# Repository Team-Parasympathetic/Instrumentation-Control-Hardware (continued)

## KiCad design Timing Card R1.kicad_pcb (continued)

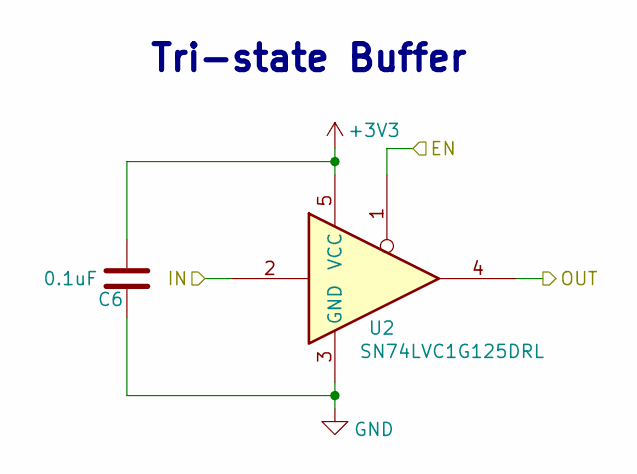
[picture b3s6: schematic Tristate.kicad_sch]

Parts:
C6: 0.1uF; C_0805_2012Metric
U2: SN74LVC1G125DRL; Texas_R-PDSO-N5_DRL-5

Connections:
/FPGA/CS: U2.1; also elsewhere on the board
/FPGA/SO/SPISO: U2.2; also elsewhere on the board
/FPGA/Tristate/OUT: U2.4; also elsewhere on the board

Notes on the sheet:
Tri-state Buffer

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
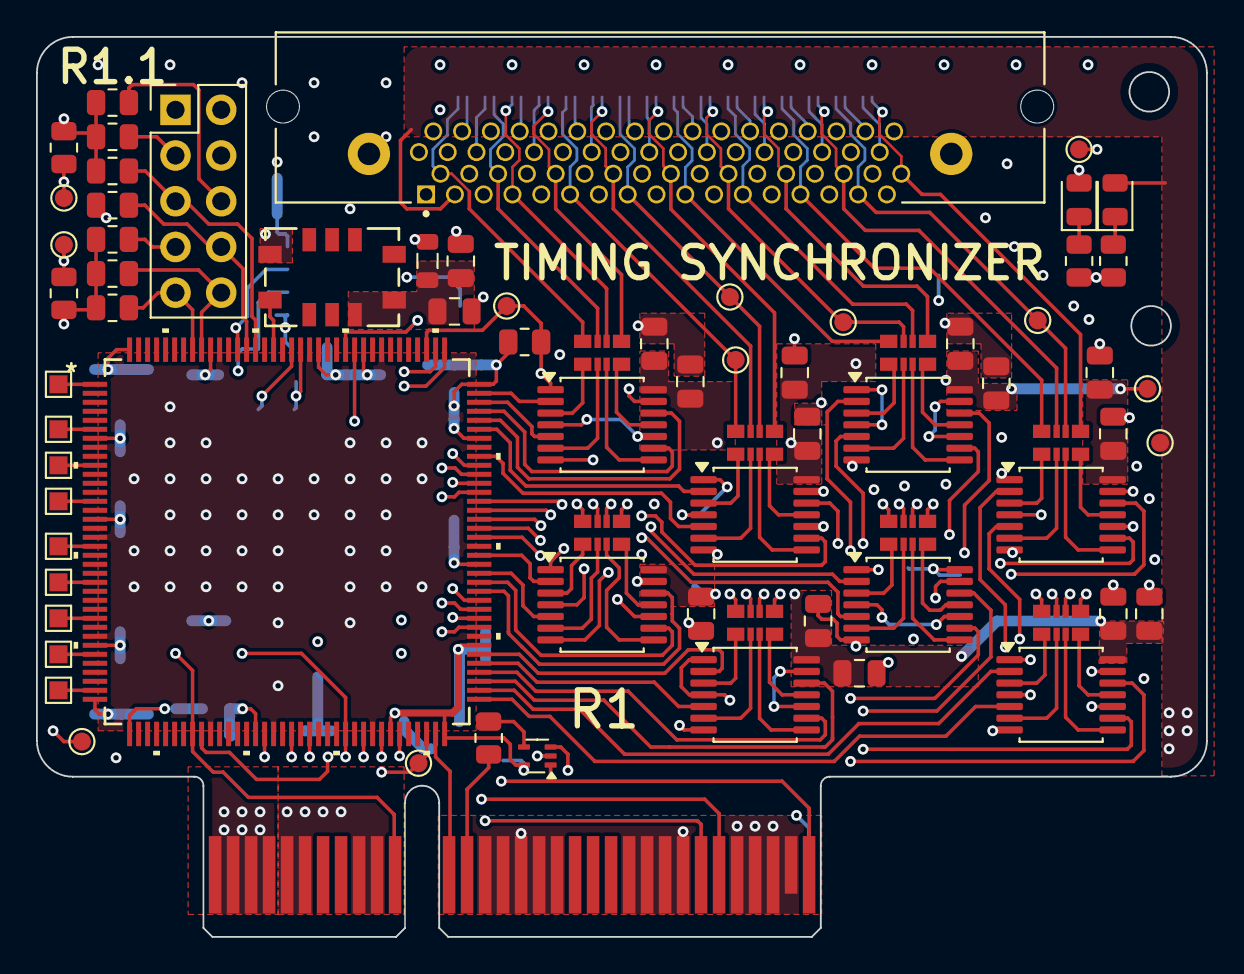
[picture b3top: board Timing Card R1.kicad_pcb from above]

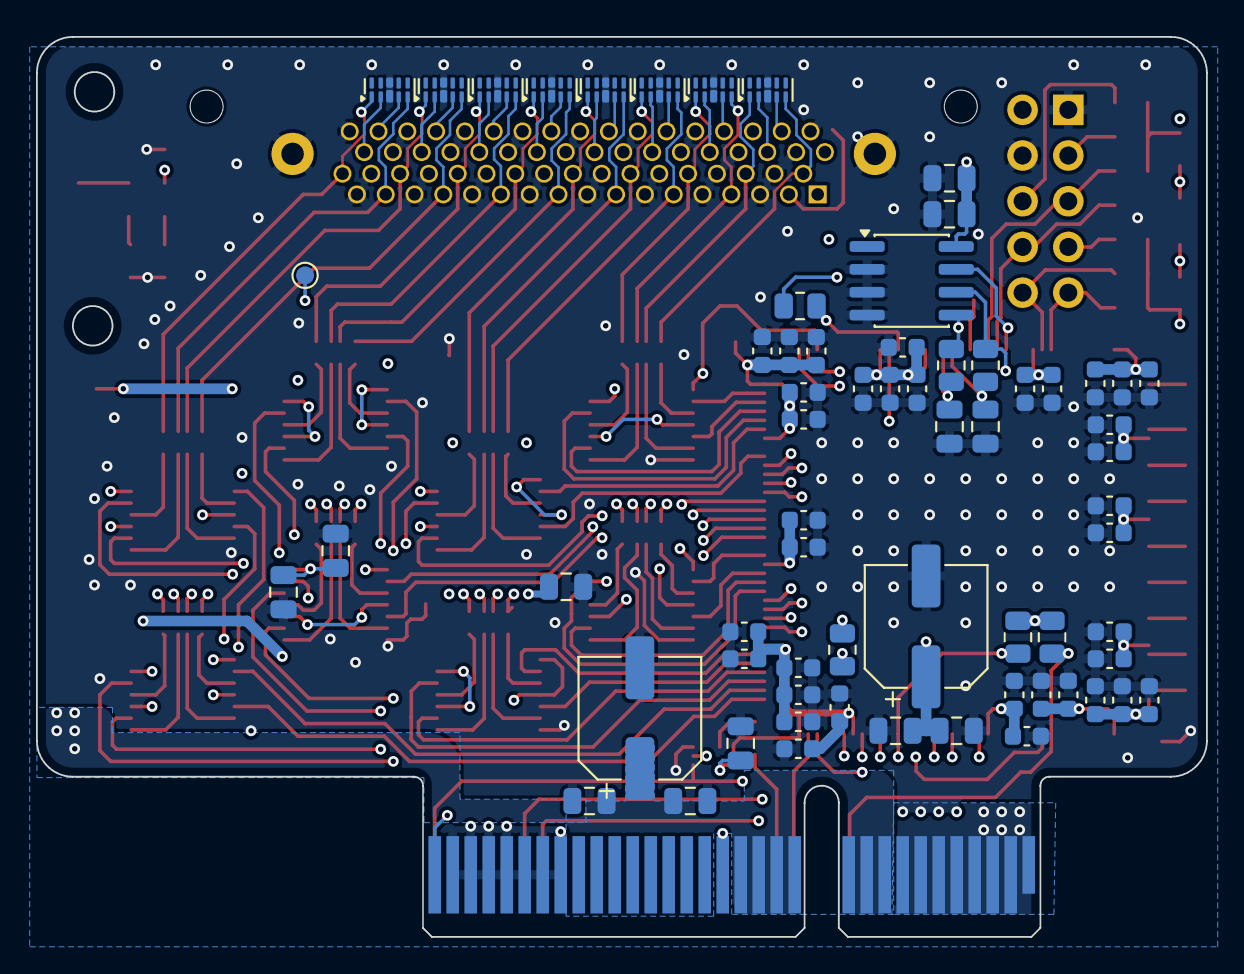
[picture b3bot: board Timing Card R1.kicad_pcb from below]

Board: 4 copper layers, 65.0 x 50.0 mm, 140 parts (66 on the bottom side), 136 nets.

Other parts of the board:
C88, C91: 0.1uF; C_0805_2012Metric
C89, C93: 1uF; C_0805_2012Metric
C90, C96: 10uF; CP_Elec_6.3x5.9
J10: 10018784-10201TLF; BUS_PCIexpress_x4

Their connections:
+5V: C91.1, C93.1, C96.1, J10.A9, J10.A10, J10.A11, J10.A12, J10.A13, J10.A14, J10.A15; also elsewhere on the board
/FPGA/CS: J10.B32; also elsewhere on the board
/FPGA/IRQ: J10.A32; also elsewhere on the board
/FPGA/MCLK/CCLK: J10.B11; also elsewhere on the board
/FPGA/MISO: J10.B13; also elsewhere on the board
/FPGA/RST: J10.B26; also elsewhere on the board
/FPGA/SI/SISPI: J10.B12; also elsewhere on the board
/FPGA/SYNC: J10.B27; also elsewhere on the board

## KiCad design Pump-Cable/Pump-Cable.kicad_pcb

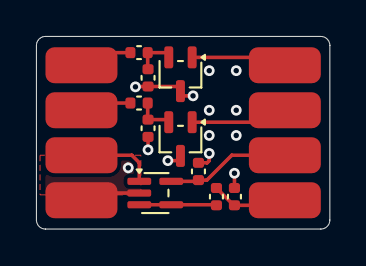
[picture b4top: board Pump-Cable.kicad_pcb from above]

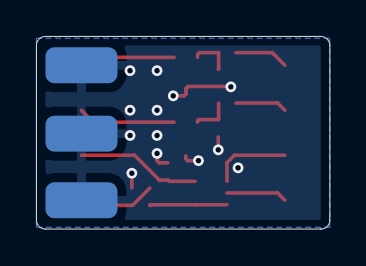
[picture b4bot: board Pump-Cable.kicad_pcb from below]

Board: 2 copper layers, 16.3 x 10.7 mm, 21 parts (3 on the bottom side), 11 nets.

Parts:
C1, C3: 100nF; C_0402_1005Metric
J1, J2, J3, J4, J5, J6, J7, J8, J9, J10, J11: Conn_01x01; SolderWirePad_1x01_SMD_2x4mm
Q1, Q2: NMOS; SOT-323_SC-70
R1, R4: 10K; C_0402_1005Metric
R2, R3, R5: 10R; C_0402_1005Metric
U2: TLV9061xDCK; SOT-353_SC-70-5

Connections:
+5V: C1.1, J11.1, U2.5 (V+)
/AIN: C3.1, J5.1, R5.2
/DAC: J1.1, U2.1 (+)
/DIR_IN: J3.1, R2.1
/DIR_OUT: J7.1, Q1.1 (D)
/EN_IN: J2.1, R3.1
/EN_OUT: J6.1, Q2.1 (D)
GND: C1.2, C3.2, J4.1, J8.1, J9.1, J10.1, Q1.3 (S), Q2.3 (S), R1.2, R4.2, U2.2 (V-)
unnamed: Q1.2 (G), R1.1, R2.2
unnamed: Q2.2 (G), R3.2, R4.1
unnamed: R5.1, U2.3 (-), U2.4

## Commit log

2026-02-17 Added ideal diodes
2026-02-18 Added USB-UART Bridge
2026-02-20 Final updates for R2
2026-02-20 Updated silkscreen
2026-06-21 libraries
2026-06-21 fdfudhf
2026-06-21 test
2026-06-21 library updates
2026-06-21 Updated libraries
2026-06-23 naming fixes
2026-06-23 Initialize instrumentation control unit repository
2026-06-23 Rename instrumentation control project to Backplane
2026-06-23 Updates on camera control card
2026-06-26 Camera Control Card layout
2026-06-27 Layout completed for camera control card
